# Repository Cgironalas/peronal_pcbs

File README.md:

# personal_pcbs
A repo where I will store pcb designs that I attempt at using

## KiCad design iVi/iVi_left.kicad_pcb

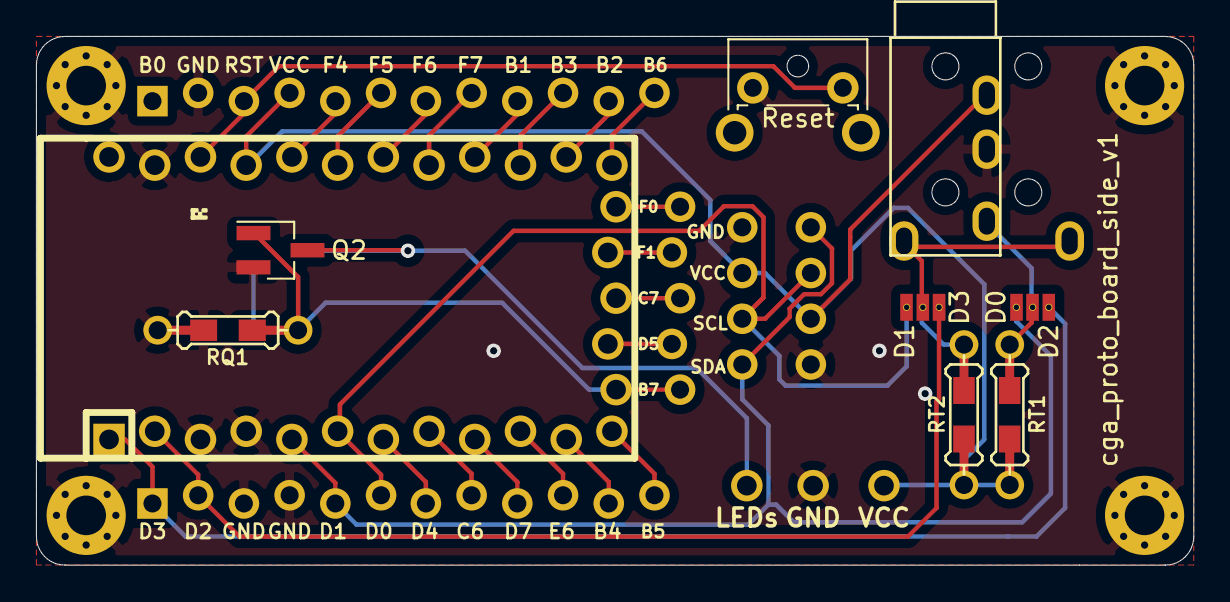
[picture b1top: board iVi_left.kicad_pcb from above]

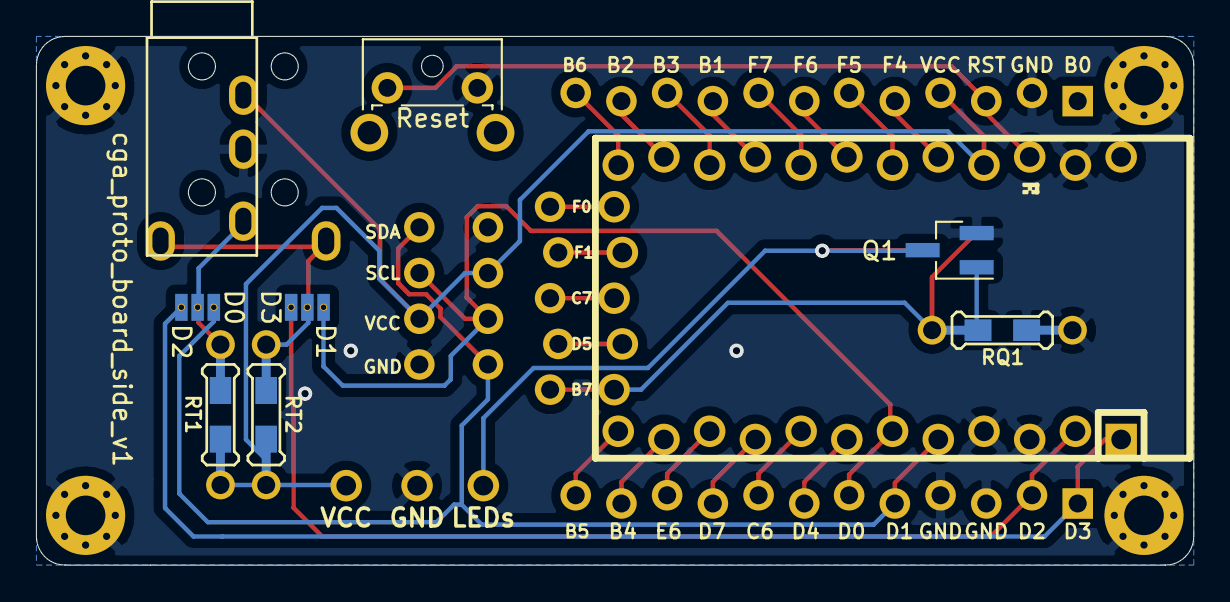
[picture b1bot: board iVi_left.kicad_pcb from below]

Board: 2 copper layers, 64.3 x 29.4 mm, 22 parts (2 on the bottom side), 29 nets.

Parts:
Cb1: Elite-C_bottom; Header-5-Pin-ZigZag
Cs1: Elite-C_left; Header-12-Pin-ZigZag-Square
Cs2: Elite-C_right; Header-12-Pin-ZigZag-Square
H1: LEDs; SinglePad
H2: GND; SinglePad
H3: VCC; SinglePad
J1, J2: 3_way_jumper; 3_way_solder_jumper
O1, O2: OLED; Header-4-Pin
Q1, Q2: 2N7002; SOT-23_Handsoldering
RQ1: 4.7k; Resistor-2-sided
RT1, RT2: 4.7k; Resistor-2-sided
Reset: SW_Push; SW_Two_sided
Screw1, Screw2, Screw3, Screw4: MountingHole_2.2mm_M2_Pad_Via
T1: TRRS; TRRS-PJ-320A-dual
U1: Elite-C; Elite-C-ZigZag

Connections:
GND: Cs1.3, Cs1.4, Cs2.2, H2.1, O1.1, O2.1, Q1.2, Q2.2, RQ1.2, Reset.2, Screw1.1, Screw2.1, Screw3.1, Screw4.1, T1.3, U1.3, U1.4, U1.23
LEDs: Cb1.1, Q1.1, Q2.1, RQ1.1, U1.25
LEDsOut: H1.1, Q1.3, Q2.3
RESET: Cs2.3, Reset.1, U1.22
RGB: Cs1.12, U1.12
RX: Cs1.2, J1.3, U1.2
SCL: Cs1.6, J1.1, O1.3, O2.3, U1.6
SDA: Cs1.5, J2.1, O1.4, O2.4, U1.5
TRRS1: J1.2, RT2.2, T1.1
TRRS2: J2.2, RT1.2, T1.2
TX: Cs1.1, J2.3, U1.1
VCC: Cs2.4, H3.1, O1.2, O2.2, RT1.1, RT2.1, T1.4, U1.21
col0: Cs2.5, U1.20
col1: Cs2.6, U1.19
col2: Cs2.7, U1.18
col3: Cs2.8, U1.17
col4: Cs2.9, U1.16
col5: Cs2.10, U1.15
col6: Cs2.11, U1.14
col7: Cs2.12, U1.13
encoder1a: Cb1.2, U1.26
encoder1b: Cb1.3, U1.27
encoder2a: Cb1.4, U1.28
encoder2b: Cb1.5, U1.29
row0: Cs1.7, U1.7
row1: Cs1.8, U1.8
row2: Cs1.9, U1.9
row3: Cs1.10, U1.10
row4: Cs1.11, U1.11

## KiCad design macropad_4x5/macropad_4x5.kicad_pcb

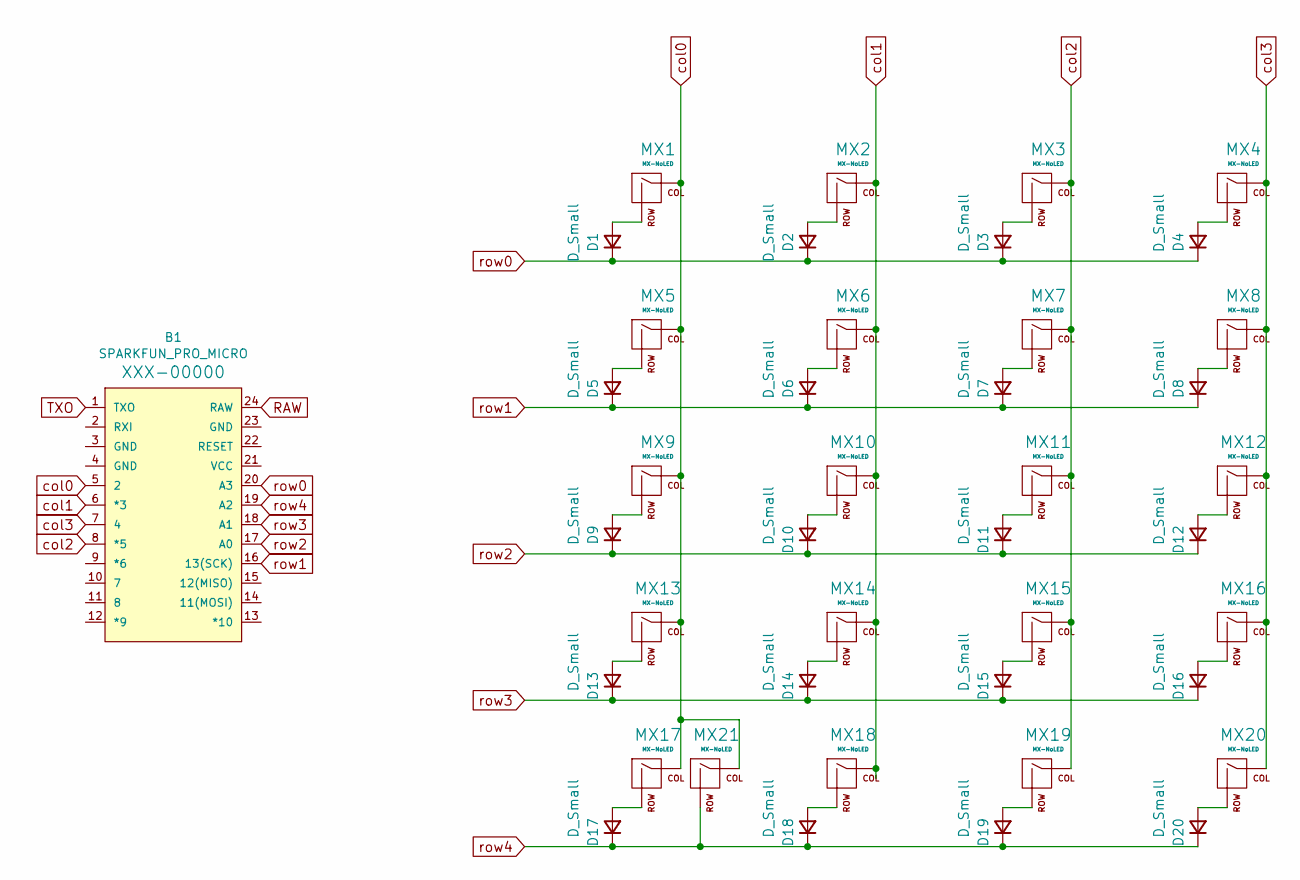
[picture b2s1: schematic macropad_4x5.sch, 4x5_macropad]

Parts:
B1: SPARKFUN_PRO_MICRO
D1, D2, D3, D4, D5, D6, D7, D8, D9, D10, D11, D12, D13, D14, D15, D16, D17, D18, D19, D20: D_Small; D_A-405_P7.62mm_Horizontal
MX1, MX2, MX3, MX4, MX5, MX6, MX7, MX8, MX9, MX10, MX11, MX12, MX13, MX14, MX15, MX16, MX17, MX18, MX19, MX20: MX-NoLED; MX-1U-NoLED
MX21: MX-NoLED; MX-2U-ReversedStabilizers-NoLED

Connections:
unnamed: D1.2 (A), MX1.2 (ROW)
unnamed: D2.2 (A), MX2.2 (ROW)
unnamed: D3.2 (A), MX3.2 (ROW)
unnamed: D4.2 (A), MX4.2 (ROW)
unnamed: D5.2 (A), MX5.2 (ROW)
unnamed: D6.2 (A), MX6.2 (ROW)
unnamed: D7.2 (A), MX7.2 (ROW)
unnamed: D8.2 (A), MX8.2 (ROW)
unnamed: D9.2 (A), MX9.2 (ROW)
unnamed: D10.2 (A), MX10.2 (ROW)
unnamed: D11.2 (A), MX11.2 (ROW)
unnamed: D12.2 (A), MX12.2 (ROW)
unnamed: D13.2 (A), MX13.2 (ROW)
unnamed: D14.2 (A), MX14.2 (ROW)
unnamed: D15.2 (A), MX15.2 (ROW)
unnamed: D16.2 (A), MX16.2 (ROW)
unnamed: D17.2 (A), MX17.2 (ROW)
unnamed: D18.2 (A), MX18.2 (ROW)
unnamed: D19.2 (A), MX19.2 (ROW)
unnamed: D20.2 (A), MX20.2 (ROW)
RAW: B1.24 (RAW)
TXO: B1.1 (TXO)
col0: B1.5 (2), MX1.1 (COL), MX5.1 (COL), MX9.1 (COL), MX13.1 (COL), MX17.1 (COL), MX21.1 (COL)
col1: B1.6 (*3), MX2.1 (COL), MX6.1 (COL), MX10.1 (COL), MX14.1 (COL), MX18.1 (COL)
col2: B1.8 (*5), MX3.1 (COL), MX7.1 (COL), MX11.1 (COL), MX15.1 (COL), MX19.1 (COL)
col3: B1.7 (4), MX4.1 (COL), MX8.1 (COL), MX12.1 (COL), MX16.1 (COL), MX20.1 (COL)
row0: B1.20 (A3), D1.1 (K), D2.1 (K), D3.1 (K), D4.1 (K)
row1: B1.16 (13(SCK)), D5.1 (K), D6.1 (K), D7.1 (K), D8.1 (K)
row2: B1.17 (A0), D9.1 (K), D10.1 (K), D11.1 (K), D12.1 (K)
row3: B1.18 (A1), D13.1 (K), D14.1 (K), D15.1 (K), D16.1 (K)
row4: B1.19 (A2), D17.1 (K), D18.1 (K), D19.1 (K), D20.1 (K), MX21.2 (ROW)

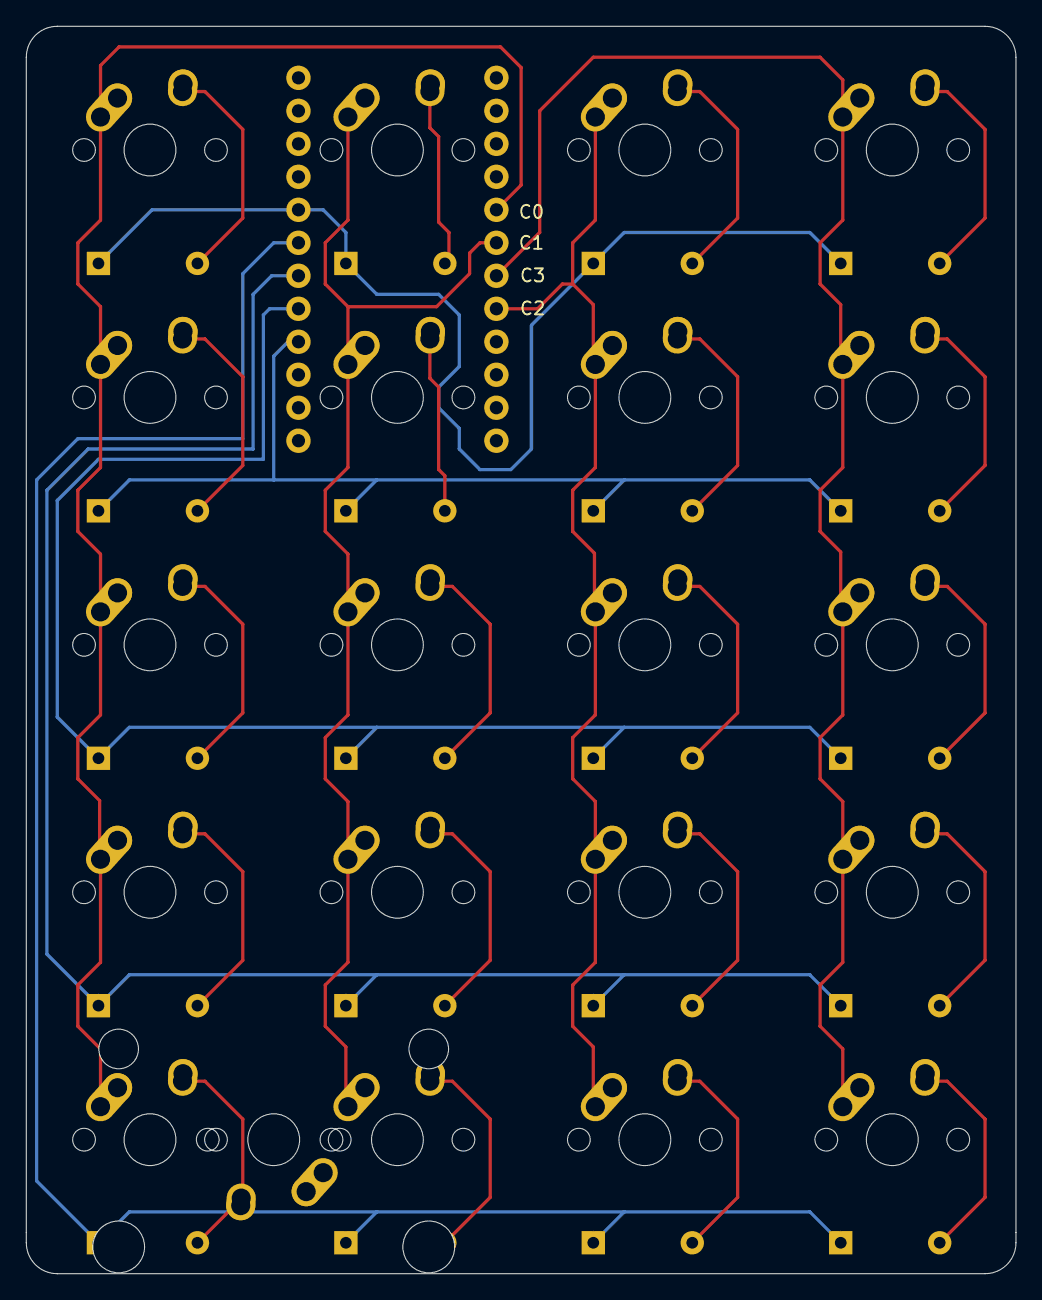
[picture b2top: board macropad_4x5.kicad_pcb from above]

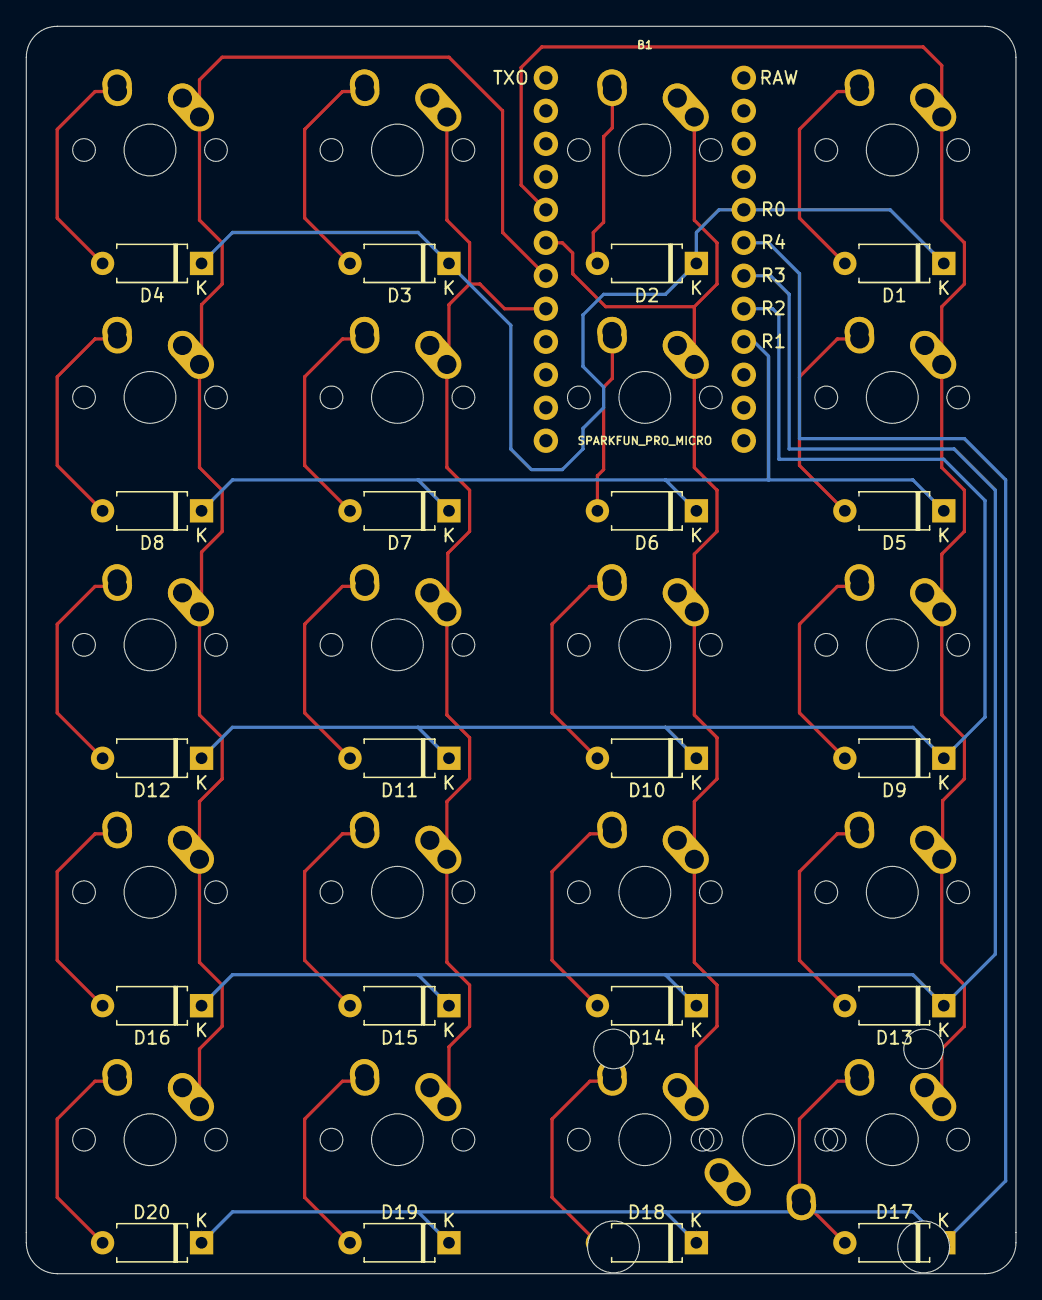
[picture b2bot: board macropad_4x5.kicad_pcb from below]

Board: 2 copper layers, 76.2 x 96.0 mm, 42 parts (21 on the bottom side), 29 nets.

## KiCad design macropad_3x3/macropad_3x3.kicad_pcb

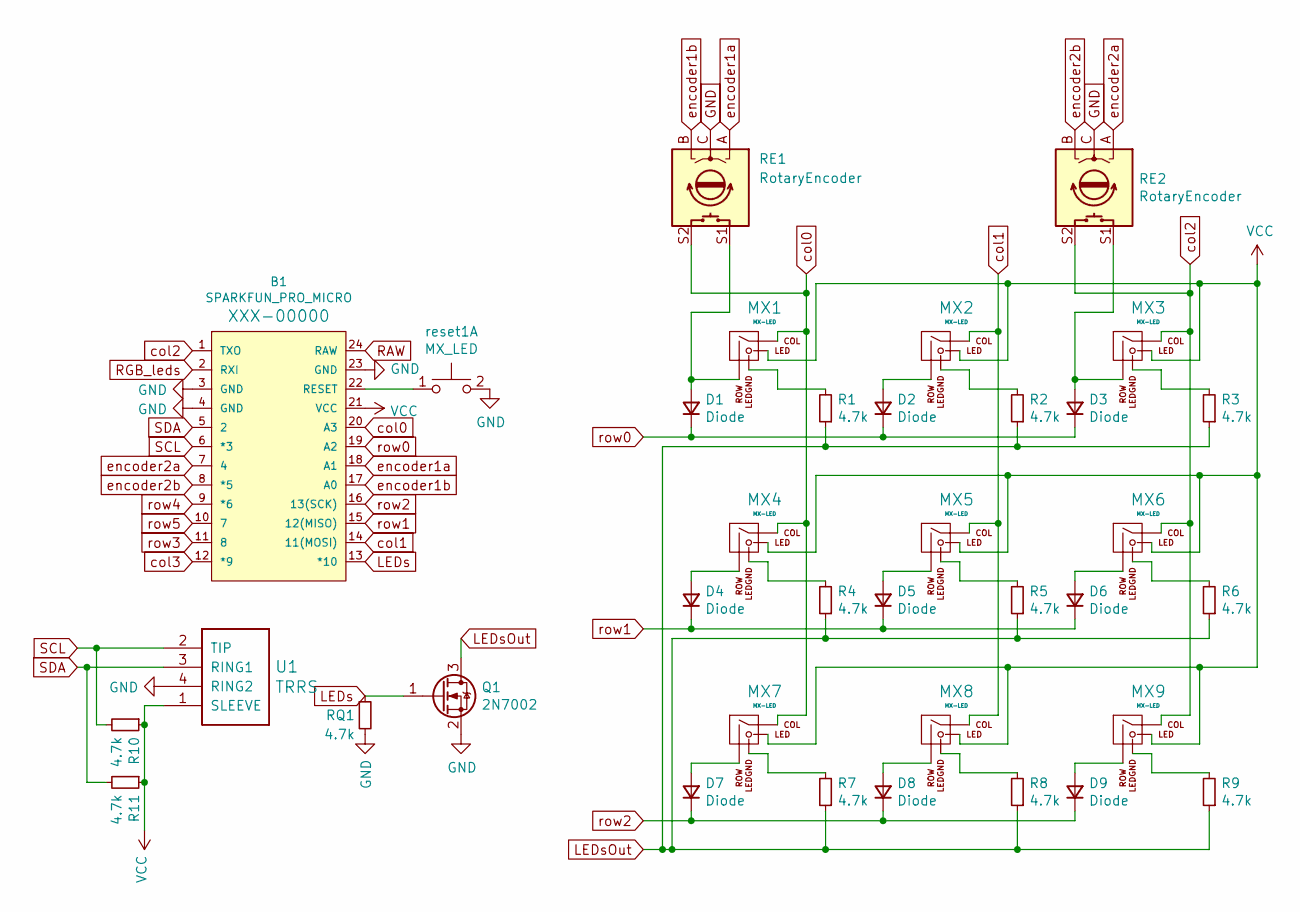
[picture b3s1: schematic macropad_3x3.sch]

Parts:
B1: SPARKFUN_PRO_MICRO
D1, D2, D3, D4, D5, D6, D7, D8, D9: Diode; Diode-Hybrid-Back
MX1, MX2, MX3, MX4, MX5, MX6, MX7, MX8, MX9: MX-LED; MX-Alps-Choc-1U
Q1: 2N7002; SOT-23_Handsoldering
R1, R2, R3, R4, R5, R6, R7, R8, R9, R10, R11: 4.7k; Resistor-Hybrid
RE1, RE2: RotaryEncoder; RotaryEncoder_EC11
RQ1: 4.7k; Resistor-Hybrid-Back
U1: TRRS; TRRS-PJ-320A
reset1: MX_LED; SW_SPST_3x3

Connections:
GND: B1.3 (GND), B1.4 (GND), B1.23 (GND), Q1.2 (S), RE1.C, RE2.C, RQ1.2, U1.4 (RING2), reset1.2
LEDs: B1.13 (*10), Q1.1 (G), RQ1.1
LEDsOut: Q1.3 (D), R1.1, R2.1, R3.1, R4.1, R5.1, R6.1, R7.1, R8.1, R9.1
unnamed: B1.22 (RESET), reset1.1
unnamed: D1.2 (A), MX1.2 (ROW), RE1.S1
unnamed: D2.2 (A), MX2.2 (ROW)
unnamed: D3.2 (A), MX3.2 (ROW), RE2.S1
unnamed: D4.2 (A), MX4.2 (ROW)
unnamed: D5.2 (A), MX5.2 (ROW)
unnamed: D6.2 (A), MX6.2 (ROW)
unnamed: D7.2 (A), MX7.2 (ROW)
unnamed: D8.2 (A), MX8.2 (ROW)
unnamed: D9.2 (A), MX9.2 (ROW)
unnamed: MX1.4 (LEDGND), R1.2
unnamed: MX2.4 (LEDGND), R2.2
unnamed: MX3.4 (LEDGND), R3.2
unnamed: MX4.4 (LEDGND), R4.2
unnamed: MX5.4 (LEDGND), R5.2
unnamed: MX6.4 (LEDGND), R6.2
unnamed: MX7.4 (LEDGND), R7.2
unnamed: MX8.4 (LEDGND), R8.2
unnamed: MX9.4 (LEDGND), R9.2
RAW: B1.24 (RAW)
RGB_leds: B1.2 (RXI)
SCL: B1.6 (*3), R10.2, U1.2 (TIP)
SDA: B1.5 (2), R11.2, U1.3 (RING1)
VCC: B1.21 (VCC), MX1.3 (LED), MX2.3 (LED), MX3.3 (LED), MX4.3 (LED), MX5.3 (LED), MX6.3 (LED), MX7.3 (LED), MX8.3 (LED), MX9.3 (LED), R10.1, R11.1, U1.1 (SLEEVE)
col0: B1.20 (A3), MX1.1 (COL), MX4.1 (COL), MX7.1 (COL), RE1.S2
col1: B1.14 (11(MOSI)), MX2.1 (COL), MX5.1 (COL), MX8.1 (COL)
col2: B1.1 (TXO), MX3.1 (COL), MX6.1 (COL), MX9.1 (COL), RE2.S2
col3: B1.12 (*9)
encoder1a: B1.18 (A1), RE1.A
encoder1b: B1.17 (A0), RE1.B
encoder2a: B1.7 (4), RE2.A
encoder2b: B1.8 (*5), RE2.B
row0: B1.19 (A2), D1.1 (K), D2.1 (K), D3.1 (K)
row1: B1.15 (12(MISO)), D4.1 (K), D5.1 (K), D6.1 (K)
row2: B1.16 (13(SCK)), D7.1 (K), D8.1 (K), D9.1 (K)
row3: B1.11 (8)
row4: B1.9 (*6)
row5: B1.10 (7)

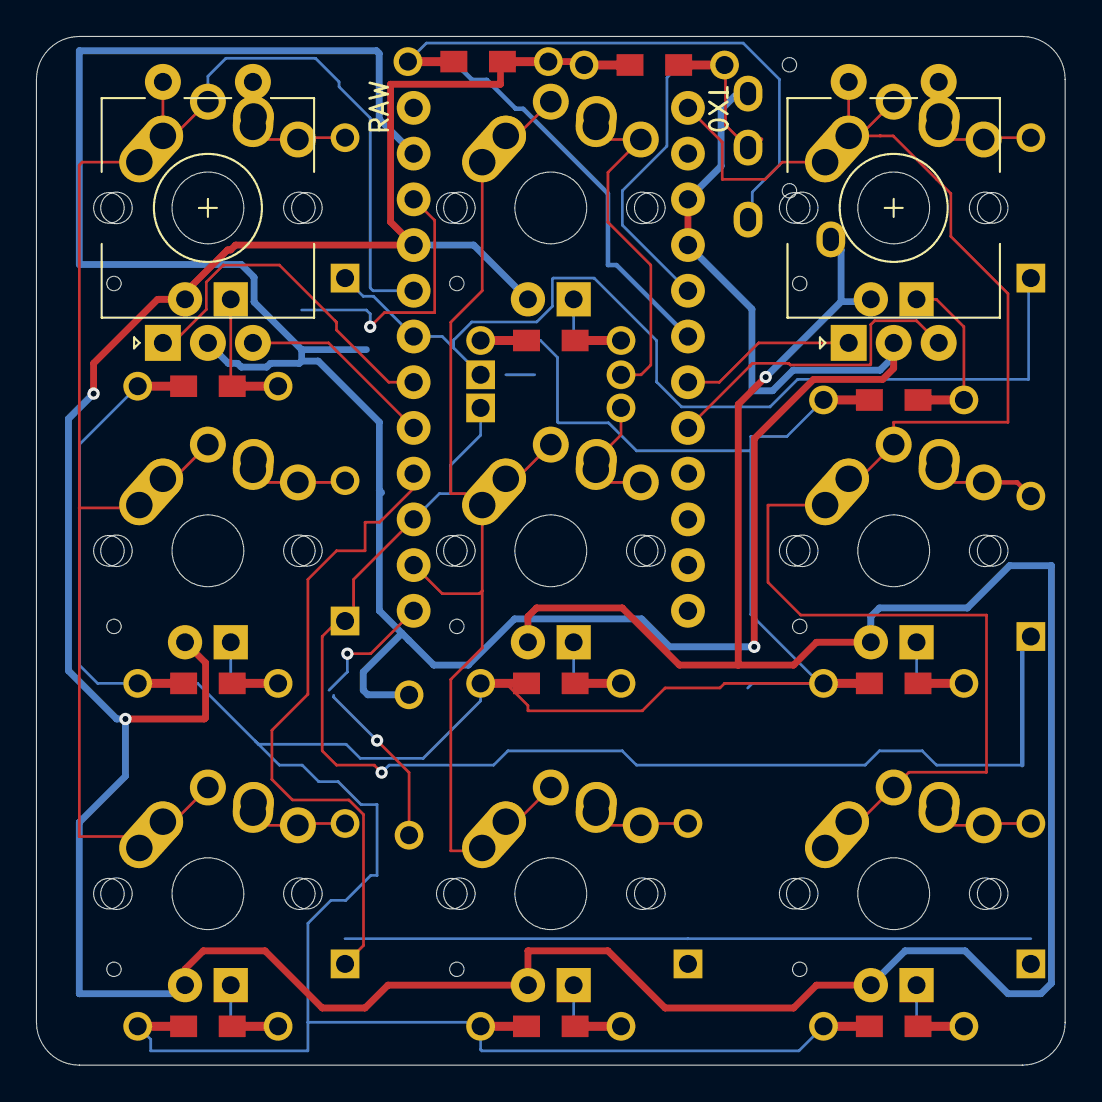
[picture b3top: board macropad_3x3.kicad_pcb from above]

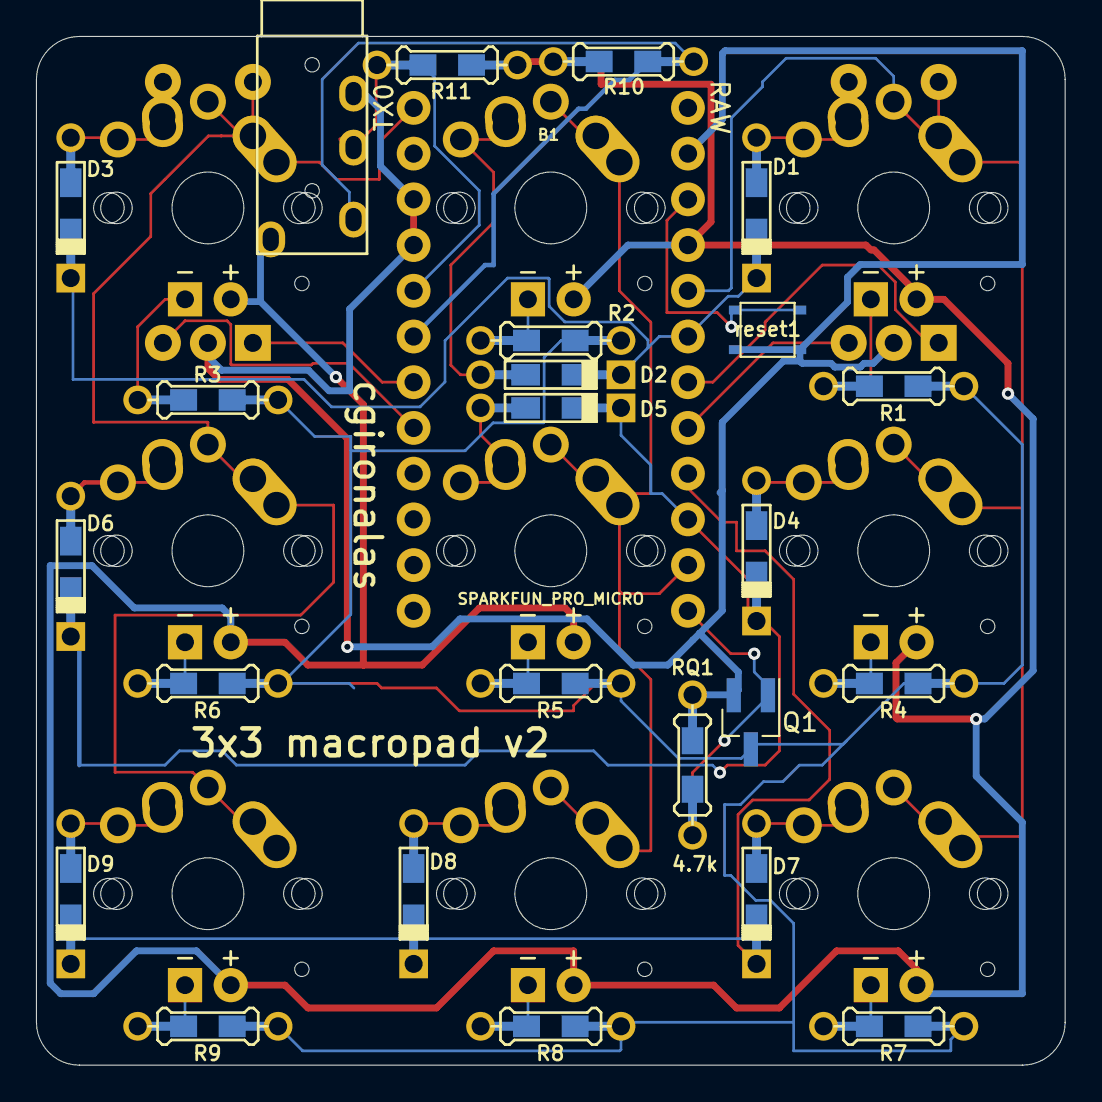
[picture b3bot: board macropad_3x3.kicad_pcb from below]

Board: 2 copper layers, 57.1 x 57.1 mm, 36 parts (15 on the bottom side), 35 nets.

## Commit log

2020-09-05 Fixed repo name
2020-09-06 Base kicad files for 3x3 macropad
2020-09-06 Add submodules
2020-09-06 Added external libraries to project
2020-09-06 Added SparkFun kicad libraries
2020-09-06 Add some sparkfun libraries to project
2020-09-06 Base schematic
    Uses the SparkFun pro micro model to simplify things, also includes the
    matrix for the 4x5 macropad.
2020-09-06 Assigned footprints to schematic
2020-09-06 Cache lib
2020-09-06 Renamed for proper project name
2020-09-06 Renamed directory for project
2020-09-06 Update to THT diodes
2020-09-06 General component placement
2020-09-06 Updated schematic and pcb routing
2020-09-07 Updated schematics and pcb design to clean it up
2020-09-07 Updated PCB
    The pro micro was facing the wrong way previously. Also added more text
    to the silk layers to help marking for use.
2020-09-08 Updated files for some comments
2020-11-14 4x5 macropad final pcb updates
2020-11-14 Large macropad v1 gerbers
2020-11-17 Added new submodules
2020-11-18 Rename v1.0 gerbers file
2020-12-10 3x3 macropad v1 gerbers
    The project files got lost in non version managed limbo. This gerber files are a close equivalent to the v1 gerbers for the 4x5 macropad.
2020-12-10 3x3 macropad project files (v2b1)
    Kicad project files for the 3x3 macropad up to date with version 2 beta 1. It's a beta version due to me testing out adding compatibility for 2 rotary encoders, pre key backlight and possibly I2C "sp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
2020-12-10 Delete macropad_3x3.pro
    Remove bad project file present in 4x5 macropad directory
2020-12-10 Add schematic pdf for 4x5 macropad v1
2020-12-19 3x3 macropad v2b1 gerbers
2020-12-19 3x3 macropad v2
    Updated the 3x3 macropad project to fix the issue with the rotary encoders causing the top corners to always be bridged. Slightly moved the TRRS jack further from the top right switch to give a bit m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
2020-12-19 Will manage gerbers through releases
2020-12-19 Upadate 3x3 macropad v2 schematic PDF
2020-12-19 3x3 macropad v2 gerbers
2020-12-27 Pro Micro Alice base project files
2020-12-27 Schematic for PM Alice
2020-12-27 Fix annotations (pm alice)
2020-12-27 Kicad annotation for pm alice schematic
2020-12-27 PM alice schematic layout
    Managed to get a reference file uploaded to the schematic to attempt to get the switches as close to a reference as possible. Added some basic cabling for the switch pins.
2020-12-27 Renamed personal pro micro alice project
2020-12-27 Trying the ZigZag PM footprint
2020-12-27 Wired columns and resistors (WIP)
2020-12-28 Worked on some more wiring
    Currently very messy, will probably try removing most of the wires and re-do everything
2020-12-29 CGA PM Alice attempt of better routing
2020-12-29 CGA PM Alice pre-joint blocks
2020-12-29 Another botchy attempt
2021-05-24 Add project for proto boards
2021-05-28 Finalize v1 of the sideways cga proto board
2021-05-28 Created top facing cga proto boards v1
2021-05-28 Add cga proto boards gerbers and PCB renders
2021-05-28 Add schematics PDF for cga proto boards
2022-07-12 Update cga_pm_alice dependencies
2022-07-12 Update cga_pm_alice files to linux
2022-07-12 Minor updates to 4x5 macropad files
2022-07-12 Update cga_proto_boards dependencies to linux
2022-07-13 Add left iVi schematic
